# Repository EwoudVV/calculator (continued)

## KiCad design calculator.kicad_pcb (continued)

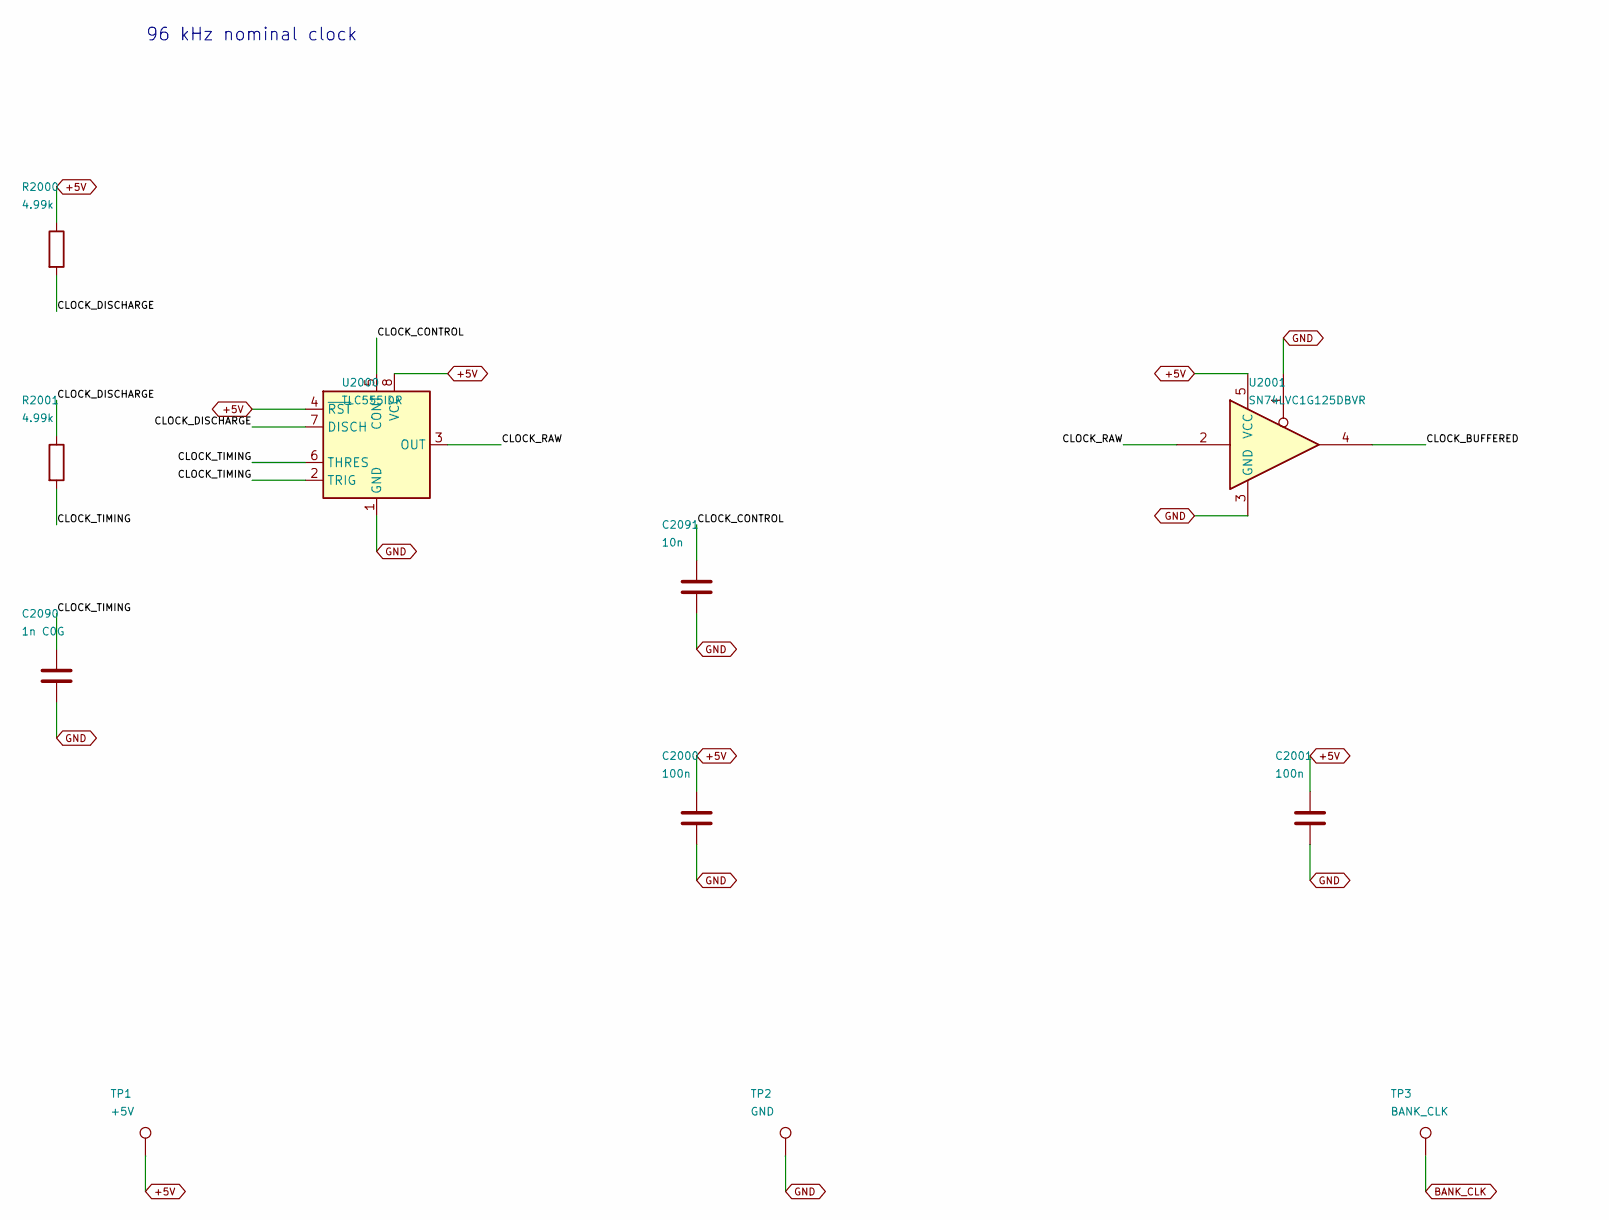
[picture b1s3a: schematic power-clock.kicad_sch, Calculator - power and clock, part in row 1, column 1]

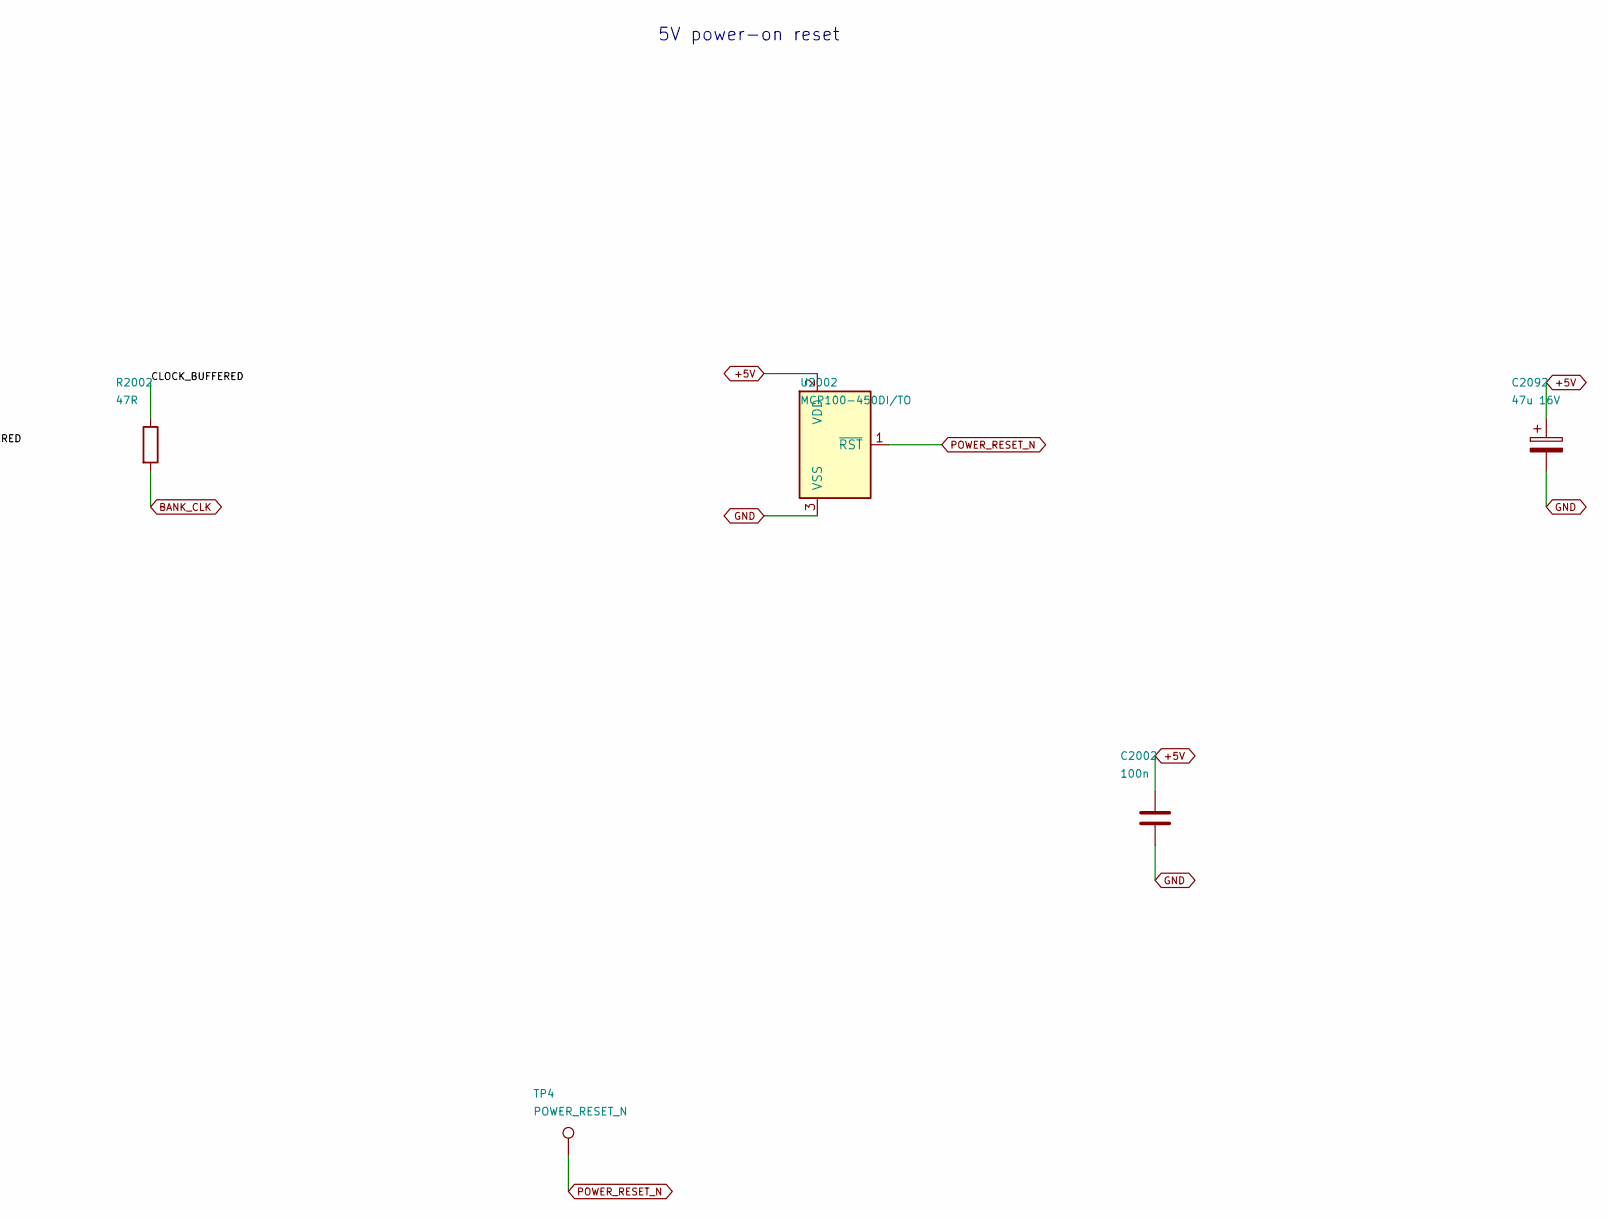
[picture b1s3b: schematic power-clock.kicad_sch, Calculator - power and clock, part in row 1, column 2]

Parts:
C2000, C2001, C2002: 100n; C_0603_1608Metric
C2090: 1n C0G; C_0603_1608Metric
C2091: 10n; C_0603_1608Metric
C2092: 47u 16V; CP_Radial_D5.0mm_P2.00mm
R2000, R2001: 4.99k; R_0603_1608Metric
R2002: 47R; R_0603_1608Metric
TP1: +5V; TestPoint_Pad_D1.5mm
TP2: GND; TestPoint_Pad_D1.5mm
TP3: BANK_CLK; TestPoint_Pad_D1.5mm
TP4: POWER_RESET_N; TestPoint_Pad_D1.5mm
U2000: TLC555IDR; SOIC-8_3.9x4.9mm_P1.27mm
U2001: SN74LVC1G125DBVR; SOT-23-5
U2002: MCP100-450DI/TO; TO-92_Inline

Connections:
+5V: C2000.1, C2001.1, C2002.1, C2092.1, R2000.1, TP1.1, U2000.4 (~RST), U2000.8 (VCC), U2001.5 (VCC), U2002.2 (VDD); also elsewhere on the board
/Power and clock/CLOCK_BUFFERED: R2002.1, U2001.4
/Power and clock/CLOCK_CONTROL: C2091.1, U2000.5 (CONT)
/Power and clock/CLOCK_DISCHARGE: R2000.2, R2001.1, U2000.7 (DISCH)
/Power and clock/CLOCK_RAW: U2000.3 (OUT), U2001.2
/Power and clock/CLOCK_TIMING: C2090.1, R2001.2, U2000.2 (TRIG), U2000.6 (THRES)
BANK_CLK: R2002.2, TP3.1; also elsewhere on the board
GND: C2000.2, C2001.2, C2002.2, C2090.2, C2091.2, C2092.2, TP2.1, U2000.1 (GND), U2001.1, U2001.3 (GND), U2002.3 (VSS); also elsewhere on the board
POWER_RESET_N: TP4.1, U2002.1 (~RST); also elsewhere on the board

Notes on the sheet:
96 kHz nominal clock
5V power-on reset

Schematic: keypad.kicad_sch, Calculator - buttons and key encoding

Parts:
C2003, C2004: 100n; C_0603_1608Metric
D2004, D2009, D2012, D2013, D2018, D2020, D2022, D2025, D2026, D2028, D2029, D2030, D2035, D2036, D2039, D2041, D2043, D2044, D2045, D2047, D2050, D2051, D2052, D2054, D2055, D2057, D2058, D2059, D2060, D2061, D2062, D2063: BAT54HGWX; D_SOD-323
R2020, R2022, R2024, R2026, R2028, R2030, R2032, R2034, R2036, R2038, R2040, R2042, R2044, R2046, R2048, R2050: 3.3k 1%; R_0603_1608Metric
R2021, R2023, R2025, R2027, R2029, R2031, R2033, R2035, R2037, R2039, R2041, R2043, R2045, R2047, R2049, R2051, R2056: 1k 1%; R_0603_1608Metric
R2052, R2053, R2054, R2055, R2063, R2064: 10k; R_0603_1608Metric
R2057, R2058: 100k 1%; R_0603_1608Metric
R2059: 12k 1%; R_0603_1608Metric
R2060, R2061: 10k 1%; R_0603_1608Metric
R2062: 6.2k 1%; R_0603_1608Metric
SW1, SW2, SW3, SW4, SW5, SW6, SW7, SW8, SW9, SW10, SW11, SW12, SW13, SW14, SW15, SW16: PTS645SM43SMTR92 LFS; SW_SPST_PTS645Sx43SMTR92
U2003: LM393BDR; SOIC-8_3.9x4.9mm_P1.27mm
U2004: SN74HC14DR; SOIC-14_3.9x8.7mm_P1.27mm

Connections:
+5V: C2003.1, C2004.1, R2020.1, R2022.1, R2024.1, R2026.1, R2028.1, R2030.1, R2032.1, R2034.1, R2036.1, R2038.1, R2040.1, R2042.1, R2044.1, R2046.1, R2048.1, R2050.1, R2052.1, R2053.1, R2054.1, R2055.1, R2056.1, R2059.1, R2061.1, R2063.1, R2064.1, U2003.8 (V+), U2004.14 (VCC); also elsewhere on the board
/Keypad/BUTTON_0: R2020.2, R2021.1, SW1.1
/Keypad/BUTTON_1: D2004.1 (K), R2022.2, R2023.1, SW2.1
/Keypad/BUTTON_2: D2009.1 (K), R2024.2, R2025.1, SW3.1
/Keypad/BUTTON_3: D2012.1 (K), D2013.1 (K), R2026.2, R2027.1, SW4.1
/Keypad/BUTTON_4: D2018.1 (K), R2028.2, R2029.1, SW5.1
/Keypad/BUTTON_5: D2020.1 (K), D2022.1 (K), R2030.2, R2031.1, SW6.1
/Keypad/BUTTON_6: D2025.1 (K), D2026.1 (K), R2032.2, R2033.1, SW7.1
/Keypad/BUTTON_7: D2028.1 (K), D2029.1 (K), D2030.1 (K), R2034.2, R2035.1, SW8.1
/Keypad/BUTTON_8: D2035.1 (K), R2036.2, R2037.1, SW9.1
/Keypad/BUTTON_9: D2036.1 (K), D2039.1 (K), R2038.2, R2039.1, SW10.1
/Keypad/BUTTON_10: D2041.1 (K), D2043.1 (K), R2040.2, R2041.1, SW11.1
/Keypad/BUTTON_11: D2044.1 (K), D2045.1 (K), D2047.1 (K), R2042.2, R2043.1, SW12.1
/Keypad/BUTTON_12: D2050.1 (K), D2051.1 (K), R2044.2, R2045.1, SW13.1
/Keypad/BUTTON_13: D2052.1 (K), D2054.1 (K), D2055.1 (K), R2046.2, R2047.1, SW14.1
/Keypad/BUTTON_14: D2057.1 (K), D2058.1 (K), D2059.1 (K), R2048.2, R2049.1, SW15.1
/Keypad/BUTTON_15: D2060.1 (K), D2061.1 (K), D2062.1 (K), D2063.1 (K), R2050.2, R2051.1, SW16.1
/Keypad/KEY_ANY_N: R2063.2, U2003.1, U2004.11
/Keypad/KEY_ANY_REF: R2059.2, R2060.1, U2003.2 (-)
/Keypad/KEY_CODE_N_0: D2004.2 (A), D2012.2 (A), D2020.2 (A), D2028.2 (A), D2036.2 (A), D2044.2 (A), D2052.2 (A), D2060.2 (A), R2052.2, U2004.1
/Keypad/KEY_CODE_N_1: D2009.2 (A), D2013.2 (A), D2025.2 (A), D2029.2 (A), D2041.2 (A), D2045.2 (A), D2057.2 (A), D2061.2 (A), R2053.2, U2004.3
/Keypad/KEY_CODE_N_2: D2018.2 (A), D2022.2 (A), D2026.2 (A), D2030.2 (A), D2050.2 (A), D2054.2 (A), D2058.2 (A), D2062.2 (A), R2054.2, U2004.5
/Keypad/KEY_CODE_N_3: D2035.2 (A), D2039.2 (A), D2043.2 (A), D2047.2 (A), D2051.2 (A), D2055.2 (A), D2059.2 (A), D2063.2 (A), R2055.2, U2004.9
/Keypad/KEY_MULTI_N: R2064.2, U2003.7, U2004.13
/Keypad/KEY_MULTI_REF: R2061.2, R2062.1, U2003.6 (-)
/Keypad/KEY_SENSE: R2021.2, R2023.2, R2025.2, R2027.2, R2029.2, R2031.2, R2033.2, R2035.2, R2037.2, R2039.2, R2041.2, R2043.2, R2045.2, R2047.2, R2049.2, R2051.2, R2056.2, R2057.1
/Keypad/KEY_SENSE_HALF: R2057.2, R2058.1, U2003.3 (+), U2003.5 (+)
GND: C2003.2, C2004.2, R2058.2, R2060.2, R2062.2, SW1.2, SW2.2, SW3.2, SW4.2, SW5.2, SW6.2, SW7.2, SW8.2, SW9.2, SW10.2, SW11.2, SW12.2, SW13.2, SW14.2, SW15.2, SW16.2, U2003.4 (V-), U2004.7 (GND); also elsewhere on the board
KEY_RAW_0: U2004.2; also elsewhere on the board
KEY_RAW_1: U2004.4; also elsewhere on the board
KEY_RAW_2: U2004.6; also elsewhere on the board
KEY_RAW_3: U2004.8; also elsewhere on the board
KEY_RAW_4: U2004.10; also elsewhere on the board
KEY_RAW_5: U2004.12; also elsewhere on the board

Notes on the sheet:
Key 0
Key 1
Key 2
Key 3
Key 4
Key 5
Key 6
Key 7
Key 8
Key 9
Key +
Key -
Key *
Key /
Key =
Key C

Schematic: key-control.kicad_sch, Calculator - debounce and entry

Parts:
C2010, C2011, C2012, C2013, C2014, C2015, C2016, C2017, C2018, C2201, C2202, C2203, C2204, C2205, C2206, C2207, C2208, C2209, C2210, C2211, C2212, C2213, C2214, C2215, C2216, C2217, C2218, C2219, C2220, C2221, C2222: 100n; C_0603_1608Metric
U2010, U2011: SN74HC174DR; SOIC-16_3.9x9.9mm_P1.27mm
U2012: SN74HC688DWR; SOIC-20W_7.5x12.8mm_P1.27mm
U2013: SN74HC4040DR; SOIC-16_3.9x9.9mm_P1.27mm
U2014, U2015: SN74HC74DR; SOIC-14_3.9x8.7mm_P1.27mm
U2016: SN74HC163DR; SOIC-16_3.9x9.9mm_P1.27mm
U2017, U2018: CD74HC173M96; SOIC-16_3.9x9.9mm_P1.27mm
U2201, U2206, U2210, U2215, U2218, U2221: SN74HC04PWR; TSSOP-14_4.4x5mm_P0.65mm
U2202, U2207, U2214, U2220: SN74HC32PWR; TSSOP-14_4.4x5mm_P0.65mm
U2203, U2211, U2216, U2219: SN74HC10DR; SOIC-14_3.9x8.7mm_P1.27mm
U2204, U2213, U2217: SN74HC08PWR; TSSOP-14_4.4x5mm_P0.65mm
U2205, U2208: CD74HC30M96; SOIC-14_3.9x8.7mm_P1.27mm
U2209: CD74HC27M96; SOIC-14_3.9x8.7mm_P1.27mm
U2212: SN74HC20DR; SOIC-14_3.9x8.7mm_P1.27mm
U2222: SN74HC00PWR; TSSOP-14_4.4x5mm_P0.65mm

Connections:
+5V: C2010.1, C2011.1, C2012.1, C2013.1, C2014.1, C2015.1, C2016.1, C2017.1, C2018.1, C2201.1, C2202.1, C2203.1, C2204.1, C2205.1, C2206.1, C2207.1, C2208.1, C2209.1, C2210.1, C2211.1, C2212.1, C2213.1, C2214.1, C2215.1, C2216.1, C2217.1, C2218.1, C2219.1, C2220.1, C2221.1, C2222.1, U2010.16 (VCC), U2011.16 (VCC), U2012.20 (VCC), U2013.16 (VDD), U2014.4 (~S), U2014.10 (~S), U2014.14 (VCC), U2015.4 (~S), U2015.10 (~S), U2015.14 (VCC), U2016.6 (D3), U2016.10 (CET), U2016.16 (VCC), U2017.12 (D2), U2017.16 (VCC), U2018.16 (VCC), U2201.14 (VCC), U2202.14 (VCC), U2203.14 (VCC), U2204.14 (VCC), U2205.6, U2205.11, U2205.12, U2205.14 (VCC), U2206.14 (VCC), U2207.14 (VCC), U2208.6, U2208.11, U2208.12, U2208.14 (VCC), U2209.14 (VCC), U2210.14 (VCC), U2211.14 (VCC), U2212.14 (VCC), U2213.14 (VCC), U2214.14 (VCC), U2215.14 (VCC), U2216.14 (VCC), U2217.14 (VCC), U2218.14 (VCC), U2219.14 (VCC), U2220.14 (VCC), U2221.14 (VCC), U2222.14 (VCC); also elsewhere on the board
/Key control/APPEND_DIGIT: U2213.4, U2213.9, U2215.2, U2220.9
/Key control/DIGIT_LOW_RANGE: U2207.5, U2209.12
/Key control/ENTRY_COUNT_0: U2016.3 (D0), U2016.14 (Q0), U2207.12
/Key control/ENTRY_COUNT_1: U2016.4 (D1), U2016.13 (Q1), U2207.13
/Key control/ENTRY_COUNT_2: U2016.5 (D2), U2016.12 (Q2), U2210.13, U2214.2, U2216.13
/Key control/ENTRY_COUNT_INC: U2016.7 (CEP), U2222.3
/Key control/ENTRY_COUNT_RESET: U2220.6, U2221.3
/Key control/ENTRY_COUNT_RESET_N: U2016.1 (~MR), U2221.4
/Key control/ENTRY_HAS_DIGITS: U2212.13, U2213.12, U2214.3, U2215.9
/Key control/ENTRY_HAS_DIGITS_OR_37: U2207.11, U2214.1
/Key control/ENTRY_RESET: U2017.15 (Mr), U2214.11, U2220.4, U2221.1
/Key control/ENTRY_RESET_OR_66: U2214.8, U2214.12
/Key control/FIFTH_DIGIT_N: U2016.9 (~PE), U2216.12
/Key control/FIRST_OPERATOR: U2213.11, U2214.4
/Key control/IS_ADD_SUB: U2206.12, U2207.9
/Key control/IS_DIGIT: U2207.6, U2211.4, U2211.10, U2216.2
/Key control/IS_EQUALS: U2210.8, U2212.10
/Key control/IS_MUL_DIV: U2207.10, U2210.4
/Key control/IS_OPERATOR: U2207.8, U2216.4
/Key control/KEY_BLOCKED: U2015.5 (Q), U2201.13, U2207.1
/Key control/KEY_BLOCKED_D: U2015.2 (D), U2204.8
/Key control/KEY_DISARMED: U2014.9 (Q), U2201.11, U2202.12
/Key control/KEY_DISARMED_D: U2014.12 (D), U2204.6
/Key control/KEY_ENTRY_READY: U2211.3, U2212.9, U2213.3, U2216.1, U2216.3
/Key control/KEY_EQUAL_N: U2012.19 (P=R), U2201.1, U2202.1
/Key control/KEY_HOLD_BLOCKED: U2204.9, U2207.3
/Key control/KEY_HOLD_DISARMED: U2202.11, U2204.4
/Key control/KEY_MATCH: U2201.2, U2203.1
/Key control/KEY_OFFER: U2202.13, U2204.12, U2206.2, U2208.1
/Key control/KEY_READY: U2204.11, U2211.9, U2213.1
/Key control/KEY_RELEASE_N: U2203.6, U2204.5, U2204.10
/Key control/KEY_SAMPLE_0_0: U2010.2 (Q0), U2011.3 (D0), U2012.2 (P0)
/Key control/KEY_SAMPLE_0_1: U2010.5 (Q1), U2011.4 (D1), U2012.4 (P1)
/Key control/KEY_SAMPLE_0_2: U2010.7 (Q2), U2011.6 (D2), U2012.6 (P2)
/Key control/KEY_SAMPLE_0_3: U2010.10 (Q3), U2011.11 (D3), U2012.8 (P3)
/Key control/KEY_SAMPLE_0_4: U2010.12 (Q4), U2011.13 (D4), U2012.11 (P4)
/Key control/KEY_SAMPLE_0_5: U2010.15 (Q5), U2011.14 (D5), U2012.13 (P5)
/Key control/KEY_SAMPLE_1_0: U2011.2 (Q0), U2012.3 (R0), U2017.14 (D0), U2018.14 (D0), U2208.2, U2210.5
/Key control/KEY_SAMPLE_1_1: U2011.5 (Q1), U2012.5 (R1), U2018.13 (D1), U2203.11, U2208.3, U2209.2, U2210.1, U2212.4
/Key control/KEY_SAMPLE_1_2: U2011.7 (Q2), U2012.7 (R2), U2017.13 (D1), U2018.12 (D2), U2206.11, U2208.4, U2209.1, U2211.2, U2212.2
/Key control/KEY_SAMPLE_1_3: U2011.10 (Q3), U2012.9 (R3), U2018.11 (D3), U2203.9, U2206.9, U2208.5, U2211.1, U2212.1
/Key control/KEY_SAMPLE_1_4: U2011.12 (Q4), U2012.12 (R4), U2205.3, U2206.3
/Key control/KEY_SAMPLE_1_5: U2011.15 (Q5), U2012.14 (R5), U2201.5, U2202.2, U2207.2
/Key control/KEY_SAMPLE_VALID: U2201.8, U2203.3, U2204.2, U2205.1
/Key control/KEY_STABLE: U2014.5 (Q), U2202.9, U2203.4, U2205.2
/Key control/KEY_STABLE_D: U2014.2 (D), U2204.3
/Key control/KEY_STABLE_OR_TIME: U2202.8, U2204.1
/Key control/KEY_TIMER_RESET: U2013.11 (Reset), U2202.6
/Key control/KEY_TIMER_RESET_OR_2: U2202.3, U2202.4
/Key control/KEY_TIME_HIGH: U2013.1 (Q11), U2202.10
/Key control/N_APPEND_DIGIT: U2211.6, U2215.1
/Key control/N_CANCEL: U2206.5, U2208.8
/Key control/N_ENTRY_COUNT_2: U2210.12, U2211.5
/Key control/N_ENTRY_HAS_DIGITS: U2215.8, U2217.1
/Key control/N_ENTRY_RESET: U2217.5, U2221.2
/Key control/N_IS_ADD_SUB: U2203.8, U2206.13
/Key control/N_IS_EQUALS: U2210.9, U2212.6
/Key control/N_IS_MUL_DIV: U2210.3, U2211.12
/Key control/N_KEY_BLOCKED: U2201.12, U2205.5
/Key control/N_KEY_DISARMED: U2201.10, U2205.4
/Key control/N_KEY_OFFER: U2205.8, U2206.1
/Key control/N_KEY_SAMPLE_1_0: U2210.6, U2212.5
/Key control/N_KEY_SAMPLE_1_1: U2210.2, U2211.13
/Key control/N_KEY_SAMPLE_1_2: U2203.10, U2206.10
/Key control/N_KEY_SAMPLE_1_3: U2206.8, U2207.4
/Key control/N_KEY_SAMPLE_1_4: U2203.5, U2206.4
/Key control/N_KEY_SAMPLE_1_5: U2201.6, U2203.2
/Key control/N_KEY_SAMPLE_VALID: U2201.9, U2203.12
/Key control/N_NEW_ENTRY: U2211.8, U2215.5
/Key control/N_OP_ACCEPT: U2017.9 (E1), U2215.11, U2216.6
/Key control/N_OP_BIT_0: U2216.10, U2218.2, U2219.4
/Key control/N_OP_BIT_1: U2216.11, U2218.4, U2219.13
/Key control/N_OP_VALID: U2213.5, U2213.13, U2215.4
/Key control/N_POWER_RESET_N: U2018.15 (Mr), U2201.4, U2202.5, U2214.9
/Key control/N_RESULT_DONE: U2210.10, U2213.2
/Key control/N_SAVE_KEY_DIGIT: U2018.9 (E1), U2221.6
/Key control/N_START_ADD: U2216.8, U2218.5
/Key control/N_START_CALC: U2212.8, U2215.13
/Key control/N_START_DIV: U2218.13, U2219.8
/Key control/N_START_MUL: U2218.11, U2219.6
/Key control/N_START_SUB: U2218.9, U2219.12
/Key control/OP_ACCEPT: U2215.10, U2220.5
/Key control/OP_BIT_0: U2017.3 (Q0), U2218.1, U2219.2, U2219.10
/Key control/OP_BIT_1: U2017.4 (Q1), U2218.3, U2219.5, U2219.11
/Key control/OP_POSITION_OK: U2214.6, U2216.5
/Key control/OP_VALID: U2017.5 (Q2), U2212.12, U2213.10, U2215.3, U2217.2
/Key control/REPLACE_OPERATOR: U2214.5, U2217.3
/Key control/RESULT_DONE: U2015.9 (Q), U2210.11, U2211.11, U2220.1
/Key control/RESULT_DONE_D: U2015.12 (D), U2217.6
/Key control/RESULT_DONE_HOLD: U2217.4, U2220.3
/Key control/SAVE_KEY_DIGIT: U2220.8, U2221.5
/Key control/START_CALC: U2215.12, U2216.9, U2219.1, U2219.3, U2219.9
BANK_CLK: U2010.9 (Cp), U2011.9 (Cp), U2013.10 (CLK), U2014.3 (C), U2014.11 (C), U2015.3 (C), U2015.11 (C), U2016.2 (CP), U2017.7 (Cp), U2018.7 (Cp); also elsewhere on the board
CANCEL: U2206.6, U2214.10; also elsewhere on the board
ENTER_A: U2213.6; also elsewhere on the board
ENTER_B: U2213.8; also elsewhere on the board
GND: C2010.2, C2011.2, C2012.2, C2013.2, C2014.2, C2015.2, C2016.2, C2017.2, C2018.2, C2201.2, C2202.2, C2203.2, C2204.2, C2205.2, C2206.2, C2207.2, C2208.2, C2209.2, C2210.2, C2211.2, C2212.2, C2213.2, C2214.2, C2215.2, C2216.2, C2217.2, C2218.2, C2219.2, C2220.2, C2221.2, C2222.2, U2010.8 (GND), U2011.8 (GND), U2012.1 (G), U2012.10 (GND), U2012.15 (P6), U2012.16 (R6), U2012.17 (P7), U2012.18 (R7), U2013.8 (VSS), U2014.7 (GND), U2015.7 (GND), U2016.8 (GND), U2017.1 (Oe1), U2017.2 (Oe2), U2017.8 (GND), U2017.10 (E2), U2017.11 (D3), U2018.1 (Oe1), U2018.2 (Oe2), U2018.8 (GND), U2018.10 (E2), U2201.7 (GND), U2202.7 (GND), U2203.7 (GND), U2204.7 (GND), U2205.7 (GND), U2206.7 (GND), U2207.7 (GND), U2208.7 (GND), U2209.3, U2209.4, U2209.5, U2209.7 (GND), U2209.9, U2209.10, U2209.11, U2209.13, U2210.7 (GND), U2211.7 (GND), U2212.7 (GND), U2213.7 (GND), U2214.7 (GND), U2215.7 (GND), U2216.7 (GND), U2217.7 (GND), U2217.12, U2217.13, U2218.7 (GND), U2219.7 (GND), U2220.7 (GND), U2220.12, U2220.13, U2221.7 (GND), U2221.9, U2221.11, U2221.13, U2222.4, U2222.5, U2222.7 (GND), U2222.9, U2222.10, U2222.12, U2222.13; also elsewhere on the board
IDLE_READY: U2204.13; also elsewhere on the board
INPUT_FULL: U2016.11 (Q3); also elsewhere on the board
KEY_DIGIT_0: U2018.3 (Q0); also elsewhere on the board
KEY_DIGIT_1: U2018.4 (Q1); also elsewhere on the board
KEY_DIGIT_2: U2018.5 (Q2); also elsewhere on the board
KEY_DIGIT_3: U2018.6 (Q3); also elsewhere on the board
KEY_RAW_0: U2010.3 (D0); also elsewhere on the board
KEY_RAW_1: U2010.4 (D1); also elsewhere on the board
KEY_RAW_2: U2010.6 (D2); also elsewhere on the board
KEY_RAW_3: U2010.11 (D3); also elsewhere on the board
KEY_RAW_4: U2010.13 (D4); also elsewhere on the board
KEY_RAW_5: U2010.14 (D5); also elsewhere on the board
NEW_ENTRY: U2214.13, U2215.6, U2220.10; also elsewhere on the board
POWER_RESET_N: U2010.1 (~Mr), U2011.1 (~Mr), U2014.1 (~R), U2014.13 (~R), U2015.1 (~R), U2015.13 (~R), U2201.3, U2203.13; also elsewhere on the board
RESULT_FINISHED: U2220.2; also elsewhere on the board
START_ADD: U2218.6; also elsewhere on the board
START_DIV: U2218.12; also elsewhere on the board
START_MUL: U2218.10; also elsewhere on the board
START_SUB: U2218.8; also elsewhere on the board
S_E_SHIFT_A_N: U2222.1; also elsewhere on the board
S_E_SHIFT_B_N: U2222.2; also elsewhere on the board

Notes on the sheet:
Gate power and local decoupling

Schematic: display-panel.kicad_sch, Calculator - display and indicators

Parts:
C2050, C2051, C2052, C2053, C2054, C2055: 100n; C_0603_1608Metric
D2200, D2201, D2202: Red 3mm; LED_D3.0mm
DS1, DS2, DS3, DS4, DS5, DS6, DS7: FJ5161AH; 7SegmentLED_LTS6760_LTS6780
R2100, R2101, R2102, R2103, R2104, R2105, R2106, R2107, R2108, R2109, R2110, R2111, R2112, R2113, R2114, R2115, R2116, R2117, R2118, R2119, R2120, R2121, R2122, R2123, R2124, R2125, R2126, R2127, R2128, R2129, R2130, R2131, R2132, R2133, R2134, R2135, R2136, R2137, R2138, R2139, R2140, R2141, R2142, R2143, R2144, R2145, R2146: 1k; R_0603_1608Metric
U2050, U2051, U2052, U2053, U2054, U2055: CD74HC4511M96; SOIC-16_3.9x9.9mm_P1.27mm
U2217: SN74HC08PWR; TSSOP-14_4.4x5mm_P0.65mm

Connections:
+5V: C2050.1, C2051.1, C2052.1, C2053.1, C2054.1, C2055.1, U2050.3 (~LT), U2050.16 (Vdd), U2051.3 (~LT), U2051.16 (Vdd), U2052.3 (~LT), U2052.16 (Vdd), U2053.3 (~LT), U2053.16 (Vdd), U2054.3 (~LT), U2054.16 (Vdd), U2055.3 (~LT), U2055.16 (Vdd); also elsewhere on the board
/Display and indicators/DISPLAY_DP_LIMITED: DS3.5 (DP), R2142.2
/Display and indicators/MINUS_SEGMENT: DS7.10 (G), R2143.2
/Display and indicators/SEG_0_A: DS1.7 (A), R2100.2
/Display and indicators/SEG_0_A_DRIVE: R2100.1, U2050.13 (Qa)
/Display and indicators/SEG_0_B: DS1.6 (B), R2101.2
/Display and indicators/SEG_0_B_DRIVE: R2101.1, U2050.12 (Qb)
/Display and indicators/SEG_0_C: DS1.4 (C), R2102.2
/Display and indicators/SEG_0_C_DRIVE: R2102.1, U2050.11 (Qc)
/Display and indicators/SEG_0_D: DS1.2 (D), R2103.2
/Display and indicators/SEG_0_D_DRIVE: R2103.1, U2050.10 (Qd)
/Display and indicators/SEG_0_E: DS1.1 (E), R2104.2
/Display and indicators/SEG_0_E_DRIVE: R2104.1, U2050.9 (Qe)
/Display and indicators/SEG_0_F: DS1.9 (F), R2105.2
/Display and indicators/SEG_0_F_DRIVE: R2105.1, U2050.15 (Qf)
/Display and indicators/SEG_0_G: DS1.10 (G), R2106.2
/Display and indicators/SEG_0_G_DRIVE: R2106.1, U2050.14 (Qg)
/Display and indicators/SEG_1_A: DS2.7 (A), R2107.2
/Display and indicators/SEG_1_A_DRIVE: R2107.1, U2051.13 (Qa)
/Display and indicators/SEG_1_B: DS2.6 (B), R2108.2
/Display and indicators/SEG_1_B_DRIVE: R2108.1, U2051.12 (Qb)
/Display and indicators/SEG_1_C: DS2.4 (C), R2109.2
/Display and indicators/SEG_1_C_DRIVE: R2109.1, U2051.11 (Qc)
/Display and indicators/SEG_1_D: DS2.2 (D), R2110.2
/Display and indicators/SEG_1_D_DRIVE: R2110.1, U2051.10 (Qd)
/Display and indicators/SEG_1_E: DS2.1 (E), R2111.2
/Display and indicators/SEG_1_E_DRIVE: R2111.1, U2051.9 (Qe)
/Display and indicators/SEG_1_F: DS2.9 (F), R2112.2
/Display and indicators/SEG_1_F_DRIVE: R2112.1, U2051.15 (Qf)
/Display and indicators/SEG_1_G: DS2.10 (G), R2113.2
/Display and indicators/SEG_1_G_DRIVE: R2113.1, U2051.14 (Qg)
/Display and indicators/SEG_2_A: DS3.7 (A), R2114.2
/Display and indicators/SEG_2_A_DRIVE: R2114.1, U2052.13 (Qa)
/Display and indicators/SEG_2_B: DS3.6 (B), R2115.2
/Display and indicators/SEG_2_B_DRIVE: R2115.1, U2052.12 (Qb)
/Display and indicators/SEG_2_C: DS3.4 (C), R2116.2
/Display and indicators/SEG_2_C_DRIVE: R2116.1, U2052.11 (Qc)
/Display and indicators/SEG_2_D: DS3.2 (D), R2117.2
/Display and indicators/SEG_2_D_DRIVE: R2117.1, U2052.10 (Qd)
/Display and indicators/SEG_2_E: DS3.1 (E), R2118.2
/Display and indicators/SEG_2_E_DRIVE: R2118.1, U2052.9 (Qe)
/Display and indicators/SEG_2_F: DS3.9 (F), R2119.2
/Display and indicators/SEG_2_F_DRIVE: R2119.1, U2052.15 (Qf)
/Display and indicators/SEG_2_G: DS3.10 (G), R2120.2
/Display and indicators/SEG_2_G_DRIVE: R2120.1, U2052.14 (Qg)
/Display and indicators/SEG_3_A: DS4.7 (A), R2121.2
/Display and indicators/SEG_3_A_DRIVE: R2121.1, U2053.13 (Qa)
/Display and indicators/SEG_3_B: DS4.6 (B), R2122.2
/Display and indicators/SEG_3_B_DRIVE: R2122.1, U2053.12 (Qb)
/Display and indicators/SEG_3_C: DS4.4 (C), R2123.2
/Display and indicators/SEG_3_C_DRIVE: R2123.1, U2053.11 (Qc)
/Display and indicators/SEG_3_D: DS4.2 (D), R2124.2
/Display and indicators/SEG_3_D_DRIVE: R2124.1, U2053.10 (Qd)
/Display and indicators/SEG_3_E: DS4.1 (E), R2125.2
/Display and indicators/SEG_3_E_DRIVE: R2125.1, U2053.9 (Qe)
/Display and indicators/SEG_3_F: DS4.9 (F), R2126.2
/Display and indicators/SEG_3_F_DRIVE: R2126.1, U2053.15 (Qf)
/Display and indicators/SEG_3_G: DS4.10 (G), R2127.2
/Display and indicators/SEG_3_G_DRIVE: R2127.1, U2053.14 (Qg)
/Display and indicators/SEG_4_A: DS5.7 (A), R2128.2
/Display and indicators/SEG_4_A_DRIVE: R2128.1, U2054.13 (Qa)
/Display and indicators/SEG_4_B: DS5.6 (B), R2129.2
/Display and indicators/SEG_4_B_DRIVE: R2129.1, U2054.12 (Qb)
/Display and indicators/SEG_4_C: DS5.4 (C), R2130.2
/Display and indicators/SEG_4_C_DRIVE: R2130.1, U2054.11 (Qc)
/Display and indicators/SEG_4_D: DS5.2 (D), R2131.2
/Display and indicators/SEG_4_D_DRIVE: R2131.1, U2054.10 (Qd)
/Display and indicators/SEG_4_E: DS5.1 (E), R2132.2
/Display and indicators/SEG_4_E_DRIVE: R2132.1, U2054.9 (Qe)
/Display and indicators/SEG_4_F: DS5.9 (F), R2133.2
/Display and indicators/SEG_4_F_DRIVE: R2133.1, U2054.15 (Qf)
/Display and indicators/SEG_4_G: DS5.10 (G), R2134.2
/Display and indicators/SEG_4_G_DRIVE: R2134.1, U2054.14 (Qg)
/Display and indicators/SEG_5_A: DS6.7 (A), R2135.2
/Display and indicators/SEG_5_A_DRIVE: R2135.1, U2055.13 (Qa)
/Display and indicators/SEG_5_B: DS6.6 (B), R2136.2
/Display and indicators/SEG_5_B_DRIVE: R2136.1, U2055.12 (Qb)
/Display and indicators/SEG_5_C: DS6.4 (C), R2137.2
/Display and indicators/SEG_5_C_DRIVE: R2137.1, U2055.11 (Qc)
/Display and indicators/SEG_5_D: DS6.2 (D), R2138.2
/Display and indicators/SEG_5_D_DRIVE: R2138.1, U2055.10 (Qd)
/Display and indicators/SEG_5_E: DS6.1 (E), R2139.2
/Display and indicators/SEG_5_E_DRIVE: R2139.1, U2055.9 (Qe)
/Display and indicators/SEG_5_F: DS6.9 (F), R2140.2
/Display and indicators/SEG_5_F_DRIVE: R2140.1, U2055.15 (Qf)
/Display and indicators/SEG_5_G: DS6.10 (G), R2141.2
/Display and indicators/SEG_5_G_DRIVE: R2141.1, U2055.14 (Qg)
/Display and indicators/STATUS_LED_0: D2200.2 (A), R2144.2
/Display and indicators/STATUS_LED_1: D2201.2 (A), R2145.2
/Display and indicators/STATUS_LED_2: D2202.2 (A), R2146.2
DISPLAY_BL_N_0: U2050.4 (~BI); also elsewhere on the board
DISPLAY_BL_N_1: U2051.4 (~BI); also elsewhere on the board
DISPLAY_BL_N_2: U2052.4 (~BI); also elsewhere on the board
DISPLAY_BL_N_3: U2053.4 (~BI); also elsewhere on the board
DISPLAY_BL_N_4: U2054.4 (~BI); also elsewhere on the board
DISPLAY_BL_N_5: U2055.4 (~BI); also elsewhere on the board
DISPLAY_DATA_0: U2050.7 (DA), U2051.7 (DA), U2052.7 (DA), U2053.7 (DA), U2054.7 (DA), U2055.7 (DA); also elsewhere on the board
DISPLAY_DATA_1: U2050.1 (DB), U2051.1 (DB), U2052.1 (DB), U2053.1 (DB), U2054.1 (DB), U2055.1 (DB); also elsewhere on the board
DISPLAY_DATA_2: U2050.2 (DC), U2051.2 (DC), U2052.2 (DC), U2053.2 (DC), U2054.2 (DC), U2055.2 (DC); also elsewhere on the board
DISPLAY_DATA_3: U2050.6 (DD), U2051.6 (DD), U2052.6 (DD), U2053.6 (DD), U2054.6 (DD), U2055.6 (DD); also elsewhere on the board
DISPLAY_DP: R2142.1; also elsewhere on the board
DISPLAY_LE_N_0: U2050.5 (~EL); also elsewhere on the board
DISPLAY_LE_N_1: U2051.5 (~EL); also elsewhere on the board
DISPLAY_LE_N_2: U2052.5 (~EL); also elsewhere on the board
DISPLAY_LE_N_3: U2053.5 (~EL); also elsewhere on the board
DISPLAY_LE_N_4: U2054.5 (~EL); also elsewhere on the board
DISPLAY_LE_N_5: U2055.5 (~EL); also elsewhere on the board
DIV_ZERO_INDICATOR: R2145.1; also elsewhere on the board
GND: C2050.2, C2051.2, C2052.2, C2053.2, C2054.2, C2055.2, D2200.1 (K), D2201.1 (K), D2202.1 (K), DS1.3 (CC), DS1.8 (CC), DS2.3 (CC), DS2.8 (CC), DS3.3 (CC), DS3.8 (CC), DS4.3 (CC), DS4.8 (CC), DS5.3 (CC), DS5.8 (CC), DS6.3 (CC), DS6.8 (CC), DS7.3 (CC), DS7.8 (CC), U2050.8 (Vss), U2051.8 (Vss), U2052.8 (Vss), U2053.8 (Vss), U2054.8 (Vss), U2055.8 (Vss); also elsewhere on the board
INPUT_FULL: R2146.1; also elsewhere on the board
NEGATIVE_SEGMENT: R2143.1, U2217.8
OVERFLOW_INDICATOR: R2144.1; also elsewhere on the board
SIGN_FLAG: U2217.9; also elsewhere on the board
STATUS_VISIBLE: U2217.10; also elsewhere on the board
